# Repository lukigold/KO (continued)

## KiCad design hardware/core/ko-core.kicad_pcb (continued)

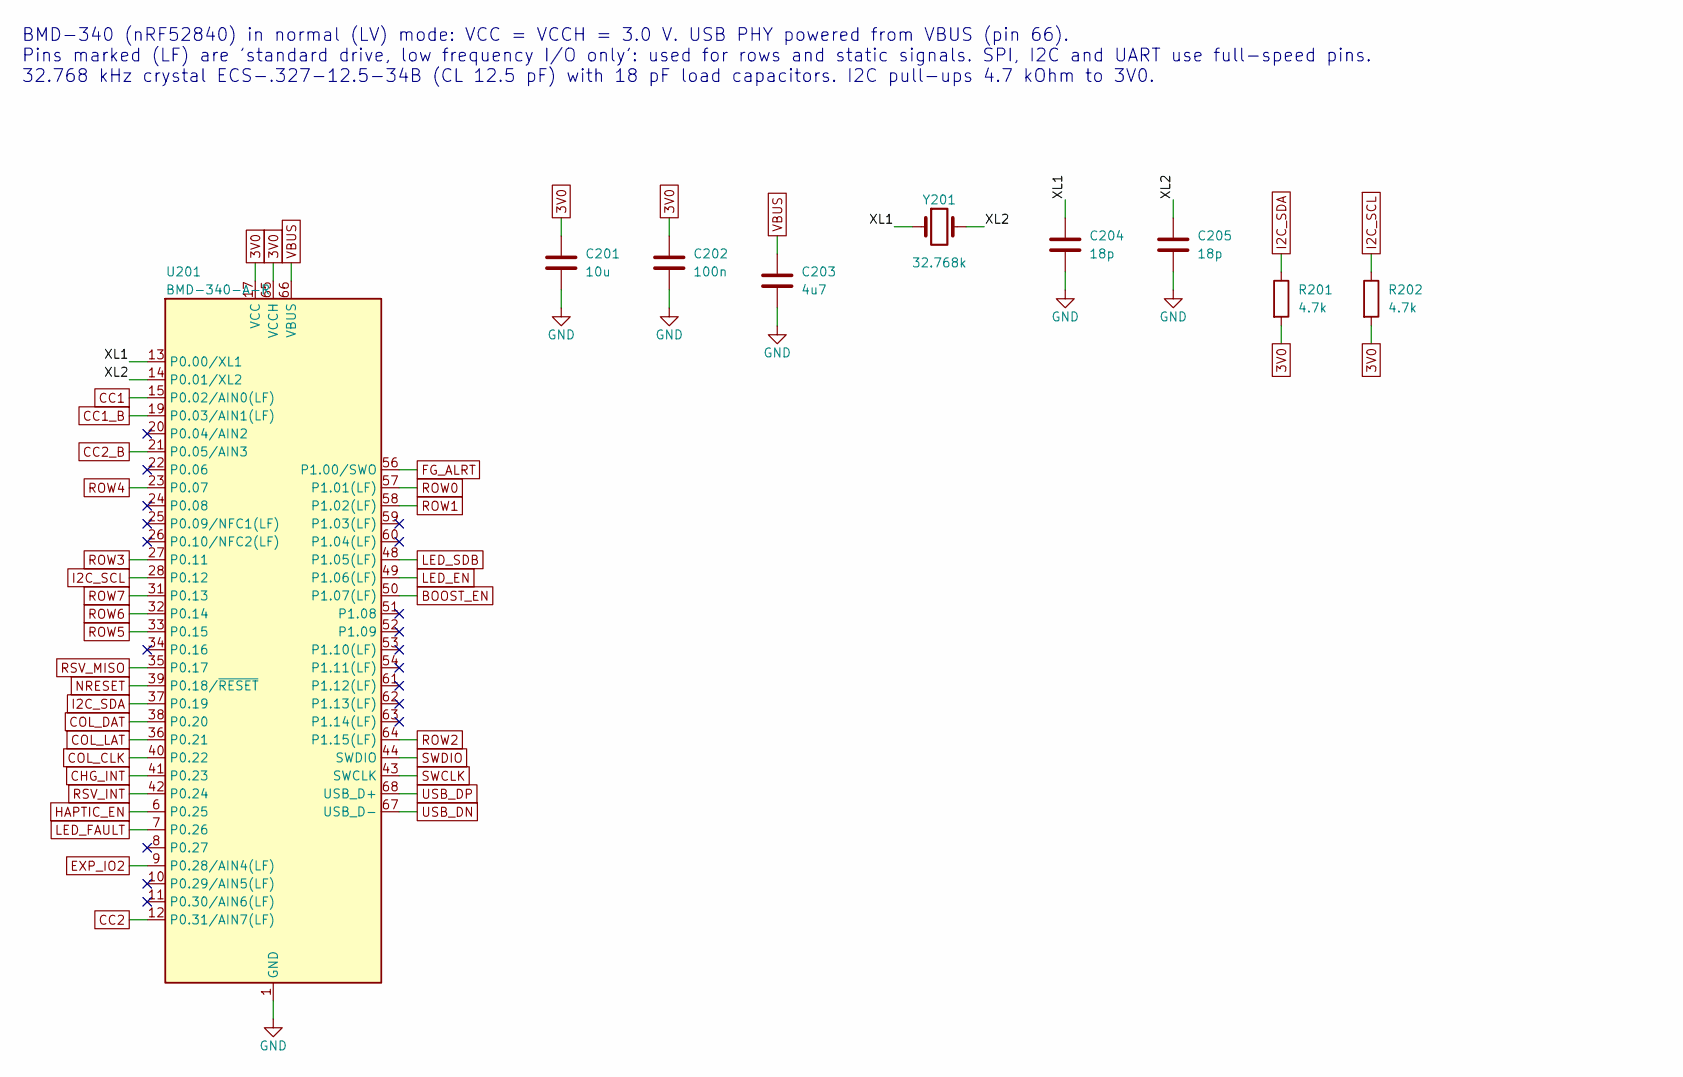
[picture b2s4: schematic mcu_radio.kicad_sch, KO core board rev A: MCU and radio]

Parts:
C201: 10u; C_0603_1608Metric; MPN CL10A106KP8NNNC; LCSC C19702
C202: 100n; C_0402_1005Metric; MPN CL05B104KO5NNNC; LCSC C1525
C203: 4u7; C_0402_1005Metric; MPN CL05A475MP5NRNC; LCSC C23733
C204, C205: 18p; C_0402_1005Metric; MPN 0402CG180J500NT; LCSC C1549
R201, R202: 4.7k; R_0402_1005Metric; MPN 0402WGF4701TCE; LCSC C25900
U201: BMD-340-A-R; u-blox_BMD-340; MPN BMD-340-A-R; LCSC C5456944
Y201: 32.768k; Crystal_SMD_3215-2Pin_3.2x1.5mm; MPN ECS-.327-12.5-34B-TR; LCSC C387600

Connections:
3V0: C201.1, C202.1, R201.2, R202.2, U201.17 (VCC), U201.65 (VCCH); also elsewhere on the board
/MCU and radio/XL1: C204.1, U201.13 (P0.00/XL1), Y201.1
/MCU and radio/XL2: C205.1, U201.14 (P0.01/XL2), Y201.2
BOOST_EN: U201.50 (P1.07(LF)); also elsewhere on the board
CC1: U201.15 (P0.02/AIN0(LF)); also elsewhere on the board
CC1_B: U201.19 (P0.03/AIN1(LF)); also elsewhere on the board
CC2: U201.12 (P0.31/AIN7(LF)); also elsewhere on the board
CC2_B: U201.21 (P0.05/AIN3); also elsewhere on the board
CHG_INT: U201.41 (P0.23); also elsewhere on the board
COL_CLK: U201.40 (P0.22); also elsewhere on the board
COL_DAT: U201.38 (P0.20); also elsewhere on the board
COL_LAT: U201.36 (P0.21); also elsewhere on the board
EXP_IO2: U201.9 (P0.28/AIN4(LF)); also elsewhere on the board
FG_ALRT: U201.56 (P1.00/SWO); also elsewhere on the board
GND: C201.2, C202.2, C203.2, C204.2, C205.2, U201.1 (GND), U201.2 (GND), U201.3 (GND), U201.4 (GND), U201.5 (GND), U201.16 (GND), U201.18 (GND), U201.29 (GND), U201.30 (GND), U201.45 (GND), U201.46 (GND), U201.47 (GND), U201.55 (GND); also elsewhere on the board
HAPTIC_EN: U201.6 (P0.25); also elsewhere on the board
I2C_SCL: R202.1, U201.28 (P0.12); also elsewhere on the board
I2C_SDA: R201.1, U201.37 (P0.19); also elsewhere on the board
LED_EN: U201.49 (P1.06(LF)); also elsewhere on the board
LED_FAULT: U201.7 (P0.26); also elsewhere on the board
LED_SDB: U201.48 (P1.05(LF)); also elsewhere on the board
NRESET: U201.39 (P0.18/~RESET); also elsewhere on the board
ROW0: U201.57 (P1.01(LF)); also elsewhere on the board
ROW1: U201.58 (P1.02(LF)); also elsewhere on the board
ROW2: U201.64 (P1.15(LF)); also elsewhere on the board
ROW3: U201.27 (P0.11); also elsewhere on the board
ROW4: U201.23 (P0.07); also elsewhere on the board
ROW5: U201.33 (P0.15); also elsewhere on the board
ROW6: U201.32 (P0.14); also elsewhere on the board
ROW7: U201.31 (P0.13); also elsewhere on the board
RSV_INT: U201.42 (P0.24); also elsewhere on the board
RSV_MISO: U201.35 (P0.17); also elsewhere on the board
SWCLK: U201.43 (SWCLK); also elsewhere on the board
SWDIO: U201.44 (SWDIO); also elsewhere on the board
USB_DN: U201.67 (USB_D-); also elsewhere on the board
USB_DP: U201.68 (USB_D+); also elsewhere on the board
VBUS: C203.1, U201.66 (VBUS); also elsewhere on the board

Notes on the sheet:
BMD-340 (nRF52840) in normal (LV) mode: VCC = VCCH = 3.0 V. USB PHY powered from VBUS (pin 66). Pins marked (LF) are 'standard drive, low frequency I/O only': used for rows and static signals. SPI, I2C and UART use full-speed pins. 32.768 kHz crystal ECS-.327-12.5-34B (CL 12.5 pF) with 18 pF load c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

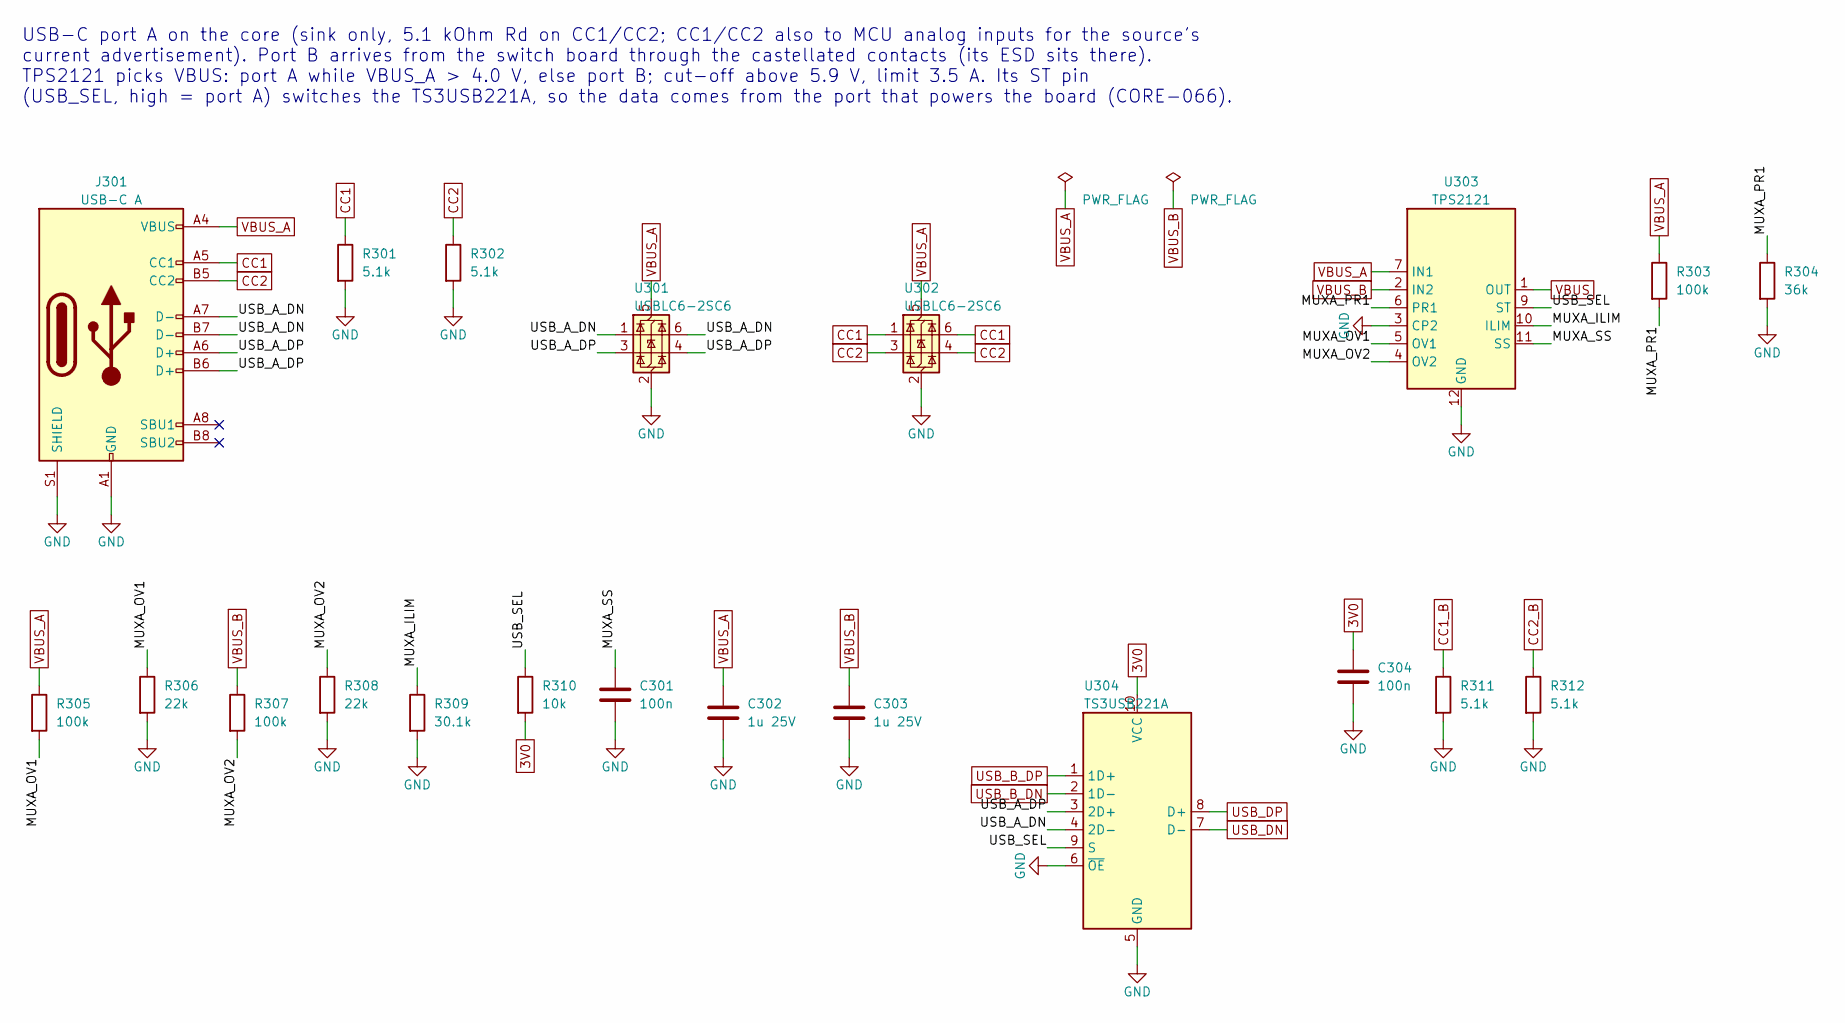
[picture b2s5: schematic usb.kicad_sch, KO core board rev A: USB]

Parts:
C301, C304: 100n; C_0402_1005Metric; MPN CL05B104KO5NNNC; LCSC C1525
C302, C303: 1u 25V; C_0402_1005Metric; MPN CL05A105KA5NQNC; LCSC C52923
J301: USB-C A; USB_C_Receptacle_HX_TYPE-C-16P_L10.0; MPN HX TYPE-C 16P L10.0; LCSC C41427495
R301, R302, R311, R312: 5.1k; R_0402_1005Metric; MPN 0402WGF5101TCE; LCSC C25905
R303, R305, R307: 100k; R_0402_1005Metric; MPN 0402WGF1003TCE; LCSC C25741
R304: 36k; R_0402_1005Metric; MPN RC0402FR-0736KL; LCSC C137999
R306, R308: 22k; R_0402_1005Metric; MPN 0402WGF2202TCE; LCSC C25768
R309: 30.1k; R_0402_1005Metric; MPN 0402WGF3012TCE; LCSC C29402
R310: 10k; R_0402_1005Metric; MPN 0402WGF1002TCE; LCSC C25744
U301, U302: USBLC6-2SC6; SOT-23-6; MPN USBLC6-2SC6; LCSC C5261088
U303: TPS2121; Texas_RUX_VQFN-HR-12_2x2.5mm; MPN TPS2121RUXR; LCSC C485916
U304: TS3USB221A; Texas_UQFN-10_1.5x2mm_P0.5mm; MPN TS3USB221ARSER; LCSC C128396

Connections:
3V0: C304.1, R310.2, U304.10 (VCC); also elsewhere on the board
/USB/MUXA_ILIM: R309.1, U303.10 (ILIM)
/USB/MUXA_OV1: R305.2, R306.1, U303.5 (OV1)
/USB/MUXA_OV2: R307.2, R308.1, U303.4 (OV2)
/USB/MUXA_PR1: R303.2, R304.1, U303.6 (PR1)
/USB/MUXA_SS: C301.1, U303.11 (SS)
/USB/USB_A_DN: J301.A7 (D-), J301.B7 (D-), U301.1 (I/O1), U301.6 (I/O1), U304.4 (2D-)
/USB/USB_A_DP: J301.A6 (D+), J301.B6 (D+), U301.3 (I/O2), U301.4 (I/O2), U304.3 (2D+)
/USB/USB_SEL: R310.1, U303.9 (ST), U304.9 (S)
CC1: J301.A5 (CC1), R301.1, U302.1 (I/O1), U302.6 (I/O1); also elsewhere on the board
CC1_B: R311.1; also elsewhere on the board
CC2: J301.B5 (CC2), R302.1, U302.3 (I/O2), U302.4 (I/O2); also elsewhere on the board
CC2_B: R312.1; also elsewhere on the board
GND: C301.2, C302.2, C303.2, C304.2, J301.A1 (GND), J301.A12 (GND), J301.B1 (GND), J301.B12 (GND), J301.S1 (SHIELD), R301.2, R302.2, R304.2, R306.2, R308.2, R309.2, R311.2, R312.2, U301.2 (GND), U302.2 (GND), U303.3 (CP2), U303.12 (GND), U304.5 (GND), U304.6 (~OE); also elsewhere on the board
USB_B_DN: U304.2 (1D-); also elsewhere on the board
USB_B_DP: U304.1 (1D+); also elsewhere on the board
USB_DN: U304.7 (D-); also elsewhere on the board
USB_DP: U304.8 (D+); also elsewhere on the board
VBUS: U303.1 (OUT), U303.8 (OUT); also elsewhere on the board
VBUS_A: C302.1, J301.A4 (VBUS), J301.A9 (VBUS), J301.B4 (VBUS), J301.B9 (VBUS), R303.1, R305.1, U301.5 (VBUS), U302.5 (VBUS), U303.7 (IN1); also elsewhere on the board
VBUS_B: C303.1, R307.1, U303.2 (IN2); also elsewhere on the board

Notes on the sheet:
USB-C port A on the core (sink only, 5.1 kOhm Rd on CC1/CC2; CC1/CC2 also to MCU analog inputs for the source's current advertisement). Port B arrives from the switch board through the castellated contacts (its ESD sits there). TPS2121 picks VBUS: port A while VBUS_A > 4.0 V, else port B; cut-off a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

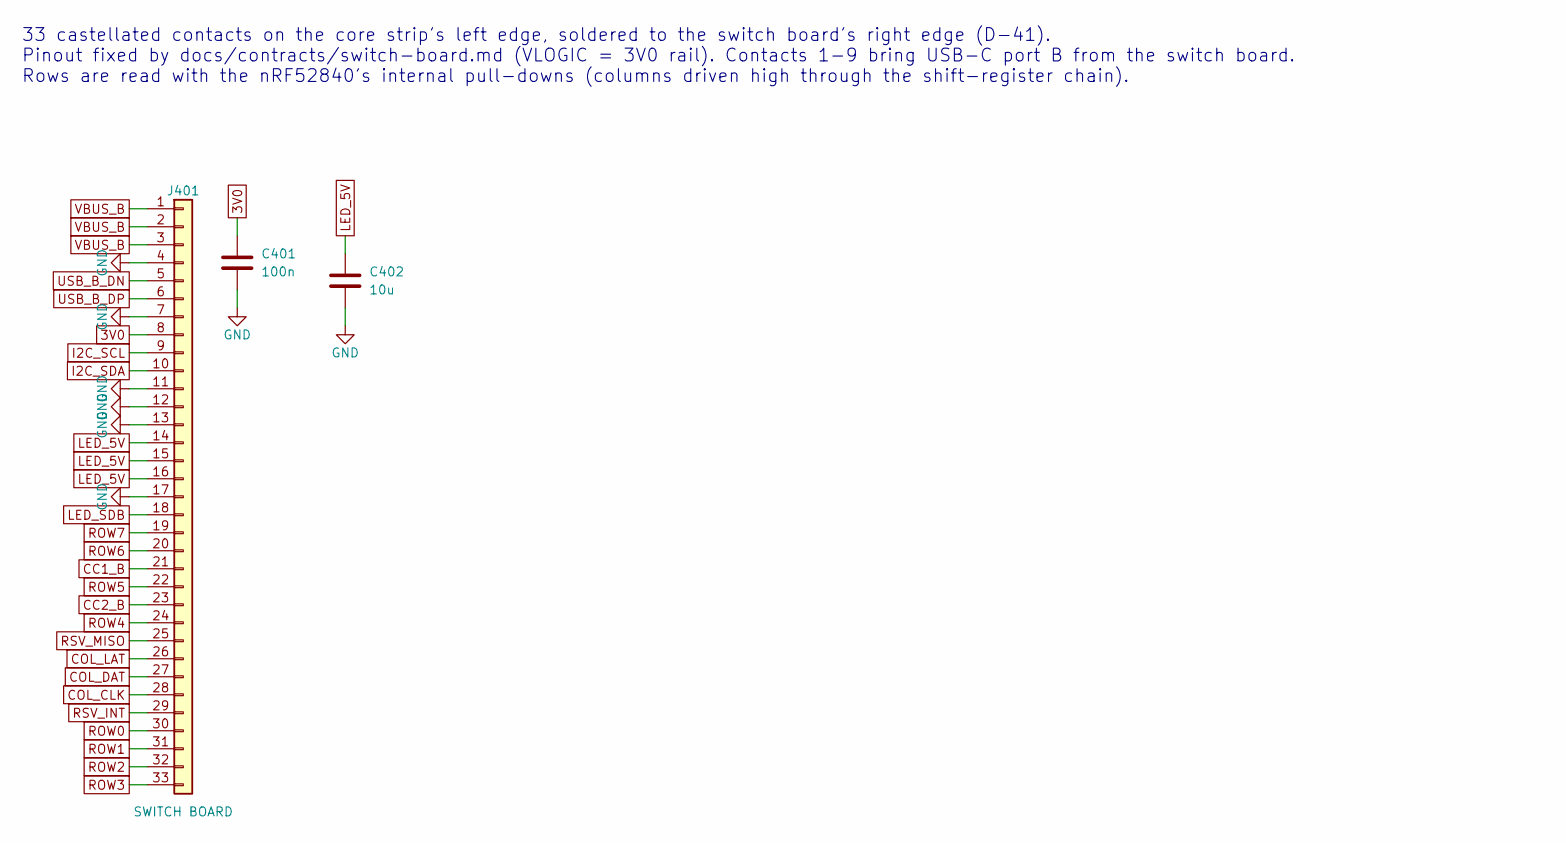
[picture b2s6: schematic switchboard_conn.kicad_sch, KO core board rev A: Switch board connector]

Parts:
C401: 100n; C_0402_1005Metric; MPN CL05B104KO5NNNC; LCSC C1525
C402: 10u; C_0603_1608Metric; MPN CL10A106KP8NNNC; LCSC C19702
J401: SWITCH BOARD; Castellated_1x33_P2.00mm_Edge_1-17_18-33

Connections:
3V0: C401.1, J401.8; also elsewhere on the board
CC1_B: J401.21; also elsewhere on the board
CC2_B: J401.23; also elsewhere on the board
COL_CLK: J401.28; also elsewhere on the board
COL_DAT: J401.27; also elsewhere on the board
COL_LAT: J401.26; also elsewhere on the board
GND: C401.2, C402.2, J401.4, J401.7, J401.11, J401.12, J401.13, J401.17; also elsewhere on the board
I2C_SCL: J401.9; also elsewhere on the board
I2C_SDA: J401.10; also elsewhere on the board
LED_5V: C402.1, J401.14, J401.15, J401.16; also elsewhere on the board
LED_SDB: J401.18; also elsewhere on the board
ROW0: J401.30; also elsewhere on the board
ROW1: J401.31; also elsewhere on the board
ROW2: J401.32; also elsewhere on the board
ROW3: J401.33; also elsewhere on the board
ROW4: J401.24; also elsewhere on the board
ROW5: J401.22; also elsewhere on the board
ROW6: J401.20; also elsewhere on the board
ROW7: J401.19; also elsewhere on the board
RSV_INT: J401.29; also elsewhere on the board
RSV_MISO: J401.25; also elsewhere on the board
USB_B_DN: J401.5; also elsewhere on the board
USB_B_DP: J401.6; also elsewhere on the board
VBUS_B: J401.1, J401.2, J401.3; also elsewhere on the board

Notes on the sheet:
33 castellated contacts on the core strip's left edge, soldered to the switch board's right edge (D-41). Pinout fixed by docs/contracts/switch-board.md (VLOGIC = 3V0 rail). Contacts 1-9 bring USB-C port B from the switch board. Rows are read with the nRF52840's internal pull-downs (columns driven h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

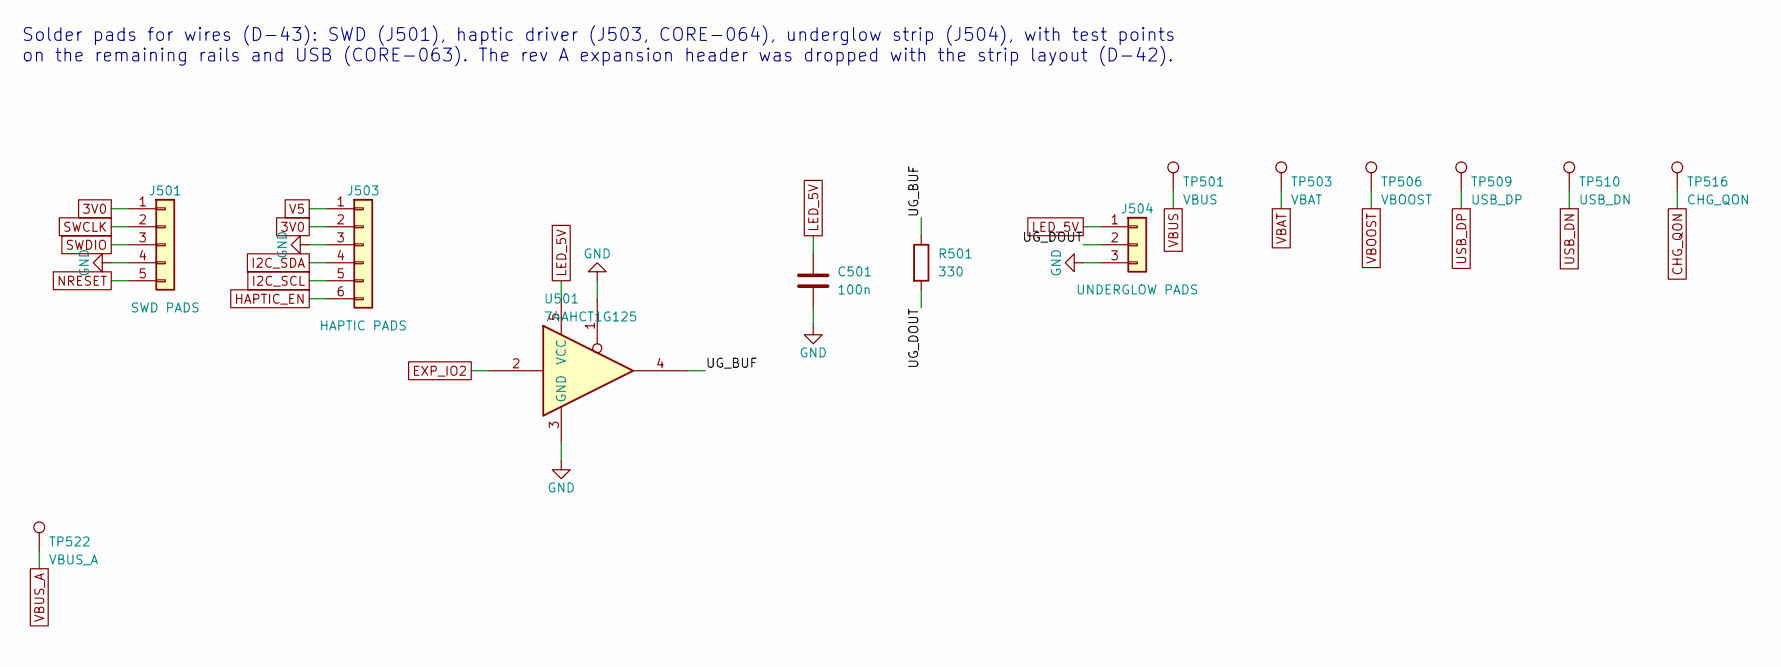
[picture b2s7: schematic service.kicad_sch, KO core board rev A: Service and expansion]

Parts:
C501: 100n; C_0402_1005Metric; MPN CL05B104KO5NNNC; LCSC C1525
J501: SWD PADS; WireGrid_SWD
J503: HAPTIC PADS; WireGrid_Haptic
J504: UNDERGLOW PADS; WirePads_Underglow
R501: 330; R_0402_1005Metric; MPN 0402WGF3300TCE; LCSC C25104
TP501: VBUS; TestPoint_Pad_D1.0mm
TP503: VBAT; TestPoint_Pad_D1.0mm
TP506: VBOOST; TestPoint_Pad_D1.0mm
TP509: USB_DP; TestPoint_Pad_D1.0mm
TP510: USB_DN; TestPoint_Pad_D1.0mm
TP516: CHG_QON; TestPoint_Pad_D1.0mm
TP522: VBUS_A; TestPoint_Pad_D1.0mm
U501: 74AHCT1G125; SOT-353_SC-70-5; MPN SN74AHCT1G125DCKR(UMW); LCSC C20617900

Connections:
3V0: J501.1, J503.2; also elsewhere on the board
/Service and expansion/UG_BUF: R501.1, U501.4
/Service and expansion/UG_DOUT: J504.2, R501.2
CHG_QON: TP516.1; also elsewhere on the board
EXP_IO2: U501.2; also elsewhere on the board
GND: C501.2, J501.4, J503.3, J504.3, U501.1, U501.3 (GND); also elsewhere on the board
HAPTIC_EN: J503.6; also elsewhere on the board
I2C_SCL: J503.5; also elsewhere on the board
I2C_SDA: J503.4; also elsewhere on the board
LED_5V: C501.1, J504.1, U501.5 (VCC); also elsewhere on the board
NRESET: J501.5; also elsewhere on the board
SWCLK: J501.2; also elsewhere on the board
SWDIO: J501.3; also elsewhere on the board
USB_DN: TP510.1; also elsewhere on the board
USB_DP: TP509.1; also elsewhere on the board
V5: J503.1; also elsewhere on the board
VBAT: TP503.1; also elsewhere on the board
VBOOST: TP506.1; also elsewhere on the board
VBUS: TP501.1; also elsewhere on the board
VBUS_A: TP522.1; also elsewhere on the board

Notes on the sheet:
Solder pads for wires (D-43): SWD (J501), haptic driver (J503, CORE-064), underglow strip (J504), with test points on the remaining rails and USB (CORE-063). The rev A expansion header was dropped with the strip layout (D-42).

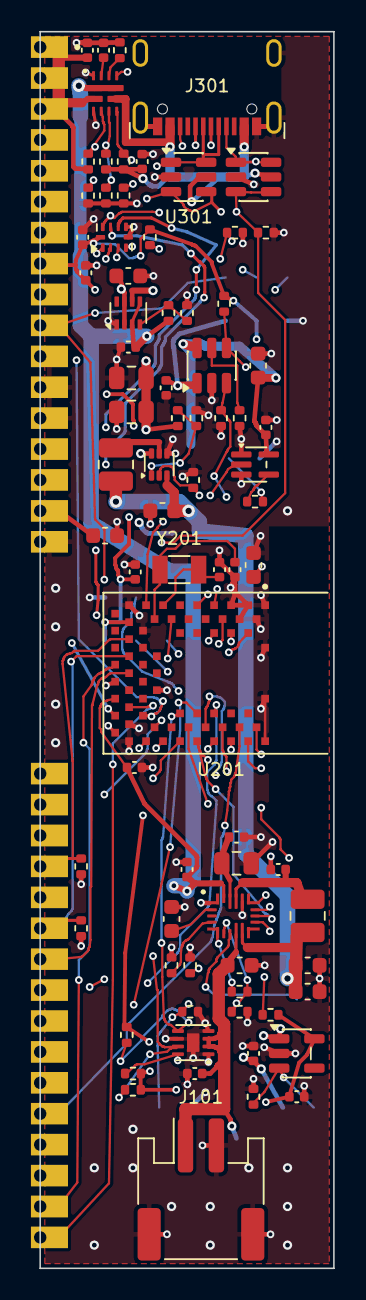
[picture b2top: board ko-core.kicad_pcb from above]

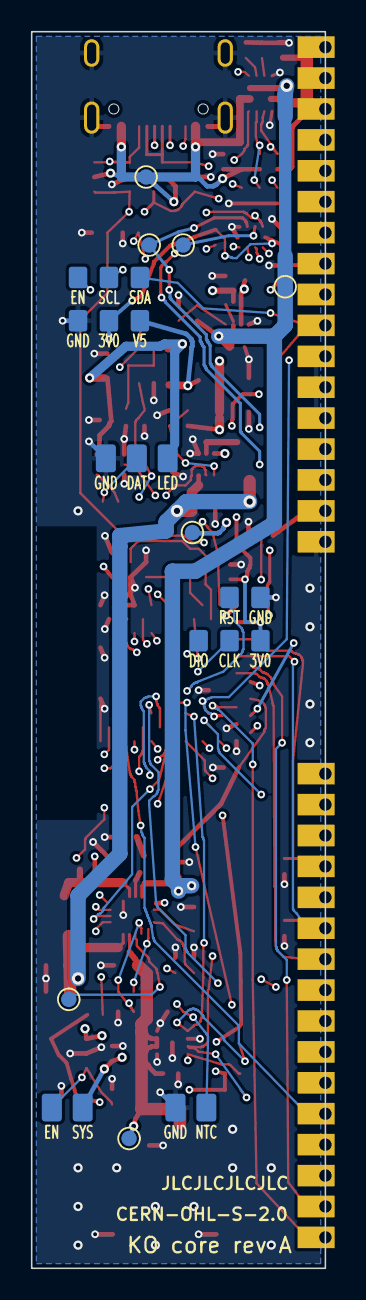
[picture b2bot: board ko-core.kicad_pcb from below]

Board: 4 copper layers, 19.0 x 80.0 mm, 91 parts (12 on the bottom side), 70 nets.

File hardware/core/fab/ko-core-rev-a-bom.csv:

Comment,Designator,Footprint,LCSC Part #
10u 25V,C102,C_0805_2012Metric,C15850
47n 25V,C104,C_0402_1005Metric,C576715
4u7,C105,C_0603_1608Metric,C19666
2u2,C111,C_0402_1005Metric,C2999759
4u7,C203,C_0402_1005Metric,C23733
1u 25V,"C101,C110,C115,C302,C303",C_0402_1005Metric,C52923
100n,"C103,C109,C117,C202,C301,C304,C401,C501",C_0402_1005Metric,C1525
10u,"C106-C108,C112,C116,C118,C201,C402",C_0603_1608Metric,C19702
22u,"C113,C114",C_0805_2012Metric,C45783
18p,"C204,C205",C_0402_1005Metric,C1549
BAT 1:+ 2:-,J101,JST_PH_S2B-PH-SM4-TB_1x02-1MP_P2.00mm_Horizontal,C54582899
USB-C A,J301,USB_C_Receptacle_HX_TYPE-C-16P_L10.0,C41427495
1u 3.5A,"L101,L102",L_1008_2520Metric,C370610
5.23k,R102,R_0402_1005Metric,C2479336
133k,R109,R_0402_1005Metric,C25753
33k,R112,R_0402_1005Metric,C25779
15k,R113,R_0402_1005Metric,C25756
36k,R304,R_0402_1005Metric,C137999
330,R501,R_0402_1005Metric,C25104
5.1k,"R101,R301,R302,R311,R312",R_0402_1005Metric,C25905
30.1k,"R103,R309",R_0402_1005Metric,C29402
10k,"R104-R106,R115,R310",R_0402_1005Metric,C25744
1M,"R107,R108",R_0402_1005Metric,C26083
100k,"R110,R111,R114,R303,R305,R307",R_0402_1005Metric,C25741
4.7k,"R201,R202",R_0402_1005Metric,C25900
22k,"R306,R308",R_0402_1005Metric,C25768
BQ25628E,U101,Texas_RYK_WQFN-HR-18,C18221178
MAX17048,U102,TDFN-8-1EP_2x2mm_P0.5mm_EP0.8x1.2mm,C2682616
TPS7A0230 (3.0 V),U103,SOT-23-5,C3747031
TPS61023,U104,SOT-563,C919459
TPS2116,U105,SOT-583-8,C3235557
AP22653,U106,SOT-23-6,C2158037
BMD-340-A-R,U201,u-blox_BMD-340,C5456944
TPS2121,U303,Texas_RUX_VQFN-HR-12_2x2.5mm,C485916
TS3USB221A,U304,Texas_UQFN-10_1.5x2mm_P0.5mm,C128396
74AHCT1G125,U501,SOT-353_SC-70-5,C20617900
USBLC6-2SC6,"U301,U302",SOT-23-6,C5261088
32.768k,Y201,Crystal_SMD_3215-2Pin_3.2x1.5mm,C387600

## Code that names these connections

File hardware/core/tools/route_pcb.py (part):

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    ("VBUS_A", F, 0.5, [(8.4, 7.15), (5.53, 7.15), (5.53, 4.35), (4.88, 4.35)]),
    ("VBUS_A", F, 0.6, [(13.2, 6.12), (13.2, 7.45)]),
    ("VBUS_A", B, 0.6, [(8.4, 7.45), (8.4, 9.4), (13.2, 9.4), (13.2, 7.45)]),
    ("VBUS_A", F, 0.3, [(10.75, 9.4), (10.15, 9.55), (9.7, 10.0), (9.7, 10.75), (9.8, 10.85), (9.8, 11.0)]),   # ESD pin 5:
    ("VBUS_A", B, 0.3, [(9.8, 11.0), (11.6, 9.4)]),                  # between its pins 3/4 to a via, back to TP522
    ("/USB/USB_A_DN", F, 0.2, [(10.55, 6.12), (10.55, 8.45)]),
    ("/USB/USB_A_DN", F, 0.2, [(11.55, 6.12), (11.55, 7.95), (10.55, 7.95)]),
    ("/USB/USB_A_DP", F, 0.2, [(10.05, 6.12), (10.05, 7.35)]),
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    ("CC2", F, 0.15, [(9.05, 6.12), (9.05, 6.95), (9.2, 7.4)]),
    ("CC2", I2, 0.15, [(9.2, 7.4), (9.2, 12.25), (12.4, 12.25), (12.7, 11.95), (12.7, 11.65)]),
    ("CC2", F, 0.15, [(12.7, 11.65), (12.66, 10.35)]),
    ("/USB/USB_SEL", F, 0.15, [(4.95, 2.85), (5.25, 2.6), (5.65, 2.6)]),   # ST pin boxed in: via to In2
    ("GND", F, 0.3, [(4.95, 22.4), (4.95, 21.2)]),                           # boost output cap C114, beside VBUS
    ("CC1_B", F, 0.2, [(1.6, 53.49), (2.65, 53.49)]),                        # port B Rd at the edge: contact 21,
    ("GND", F, 0.3, [(2.65, 54.51), (2.65, 55.15)]),                         #   its GND via against the edge
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    ("SYS", F, 0.6, [(8.2, 29.35), (8.67, 29.8), (8.67, 31.0)]),
    ("LED_5V", I2, 1.0, [(9.25, 20.2), (10.0, 20.95), (10.0, 24.4), (3.0, 24.4), (3.0, 27.0), (1.2, 27.0), (1.2, 31.0)]),
    ("LED_5V", B, 0.6, [(9.25, 20.2), (9.75, 20.7), (9.75, 26.7)]),
    ("GND", F, 0.2, [(3.45, 5.15), (3.6, 6.05)]),                    # TPS2121 GND pin 3, walled in by VBUS_B and its pins
    # GND ends of the mux dividers R308/R306/R304, joined and taken to one via on the right: fan-out vias
    # below them walled in the mux's top pins (USB_DP/USB_DN/USB_SEL leave U304 upwards)
    ("GND", F, 0.25, [(3.1, 11.11), (6.25, 11.11)]),
    # SWD out of the module's front right corner to vias right of the SYS trunk, SWDIO above SWCLK, so the
    # haptic enable from pad 41 passes below both on the top layer towards J503
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
# Charger pin escapes, in board coordinates of CHARGER_DY = 0 and moved with the charger.
_et, _ev = _moved([
    # the charger's CE, I2C and interrupt pins face a closed pocket (SW above, SYS below, L101 right): each to its
    # own via beside the pins, left of the SYS trunk on B (FRONT_TRACKS), top to bottom in pin order
    ("/Battery and charger/CHG_CE", F, 0.15, [(12.1, 54.35), (12.6, 53.85)]),   # from the L pad's foot
    ("I2C_SCL", F, 0.15, [(11.9, 54.81), (12.65, 54.81), (12.85, 54.61)]),
    ("I2C_SDA", F, 0.15, [(11.9, 55.21), (12.8, 55.21), (12.99, 55.4)]),
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
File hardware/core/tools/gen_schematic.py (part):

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s.add("U201", "ko:BMD-340", "BMD-340-A-R", {
    # pins chosen for the 16 mm strip (D-43): the module's left pad column sits at the castellated edge and only
    # keeps its fixed-function pins (VCC, VBUS, USB); rows leave through the front pad row; port B's CC lines and
    # ROW2-ROW4 use left-column pins next to their edge contacts (D-48, D-53, D-54)
    "13": "XL1", "14": "XL2", "15": "CC1", "19": "CC1_B", "20": "NC", "21": "CC2_B",   # D-48, D-53
    "22": "NC", "23": "ROW4", "24": "NC", "25": "NC", "26": "NC", "27": "ROW3", "28": "I2C_SCL",   # D-54
    # front pad row, left to right in the order of contacts 19-33 (rows 7-5, then the column chain), so the
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s = design.sheet("USB", "usb.kicad_sch", paper="A4", note=(
    "USB-C port A on the core (sink only, 5.1 kOhm Rd on CC1/CC2; CC1/CC2 also to MCU analog inputs for the source's\n"
    "current advertisement). Port B arrives from the switch board through the castellated contacts (its ESD sits there).\n"
    "TPS2121 picks VBUS: port A while VBUS_A > 4.0 V, else port B; cut-off above 5.9 V, limit 3.5 A. Its ST pin\n"
    "(USB_SEL, high = port A) switches the TS3USB221A, so the data comes from the port that powers the board (CORE-066)."))
s.add("J301", "Connector:USB_C_Receptacle_USB2.0_16P", "USB-C A", {
    "VBUS": "VBUS_A", "GND": "GND", "SHIELD": "GND", "CC1": "CC1", "CC2": "CC2", "A6": "USB_A_DP", "B6": "USB_A_DP",
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    "28": "COL_CLK", "29": "RSV_INT", "30": "ROW0", "31": "ROW1", "32": "ROW2", "33": "ROW3"}
s = design.sheet("Switch board connector", "switchboard_conn.kicad_sch", paper="A4", note=(
    "33 castellated contacts on the core strip's left edge, soldered to the switch board's right edge (D-41).\n"
    "Pinout fixed by docs/contracts/switch-board.md (VLOGIC = 3V0 rail). Contacts 1-9 bring USB-C port B from the switch board.\n"
    "Rows are read with the nRF52840's internal pull-downs (columns driven high through the shift-register chain)."))
s.add("J401", "Connector_Generic:Conn_01x33", "SWITCH BOARD", SWB_PINOUT,
      footprint="ko:Castellated_1x33_P2.00mm_Edge_1-17_18-33", in_bom=False, description="Castellated edge, no part")
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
